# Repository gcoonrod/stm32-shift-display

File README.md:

# STM32 Shift Display

A proof-of-concept STM32 based development board designed for experimentation with 74x595 driven 7-segment LED character displays. The sponsored revision of the board is built out as a desk clock, the "STM32 Shift Clock".

> **Building or hacking on this?** [`docs/DEVELOPMENT.md`](./docs/DEVELOPMENT.md) covers prerequisites, build and flash, the USB command set, the pin map, and what is still unimplemented.

## Current Revision — rev 2
Sponsored by: 

Due to a generous sponsorship from PCBWay the current hardware revision (rev 2) includes a number of substantial design changes over the first revision:
-  All SMD components from rev 0 moved to the back.
-  Most THT components from rev 0 changed to hand-solder friendly SMD components.
-  Supercap backup for VBAT switched to more common CR2032 battery holder.
-  Addition of ESD IC for the USB connection and a correction for an issue with the USB FS series and pull-up resistors.
-  Move to a 4 layer PCB and use of via-in-pad resin plug with copper capping to simplify routing.
-  Addition of an aluminum sheet metal stand.
-  Remap latch OE pin and user LED pins to PWM capable outputs.
-  Break out UART3 "just in case".

Full schematic for this revision: [STM32ShiftDisplayRev2.pdf](./hardware/assets/STM32ShiftDisplayRev2.pdf)

### Revision Objectives
Issues with the USB connection in the first revision made a new revision necessary in order to support UART communication over the USB connection. While the USB termination bug was the primary driver for spinning a new board, there were also a few other short comings of the original design that became apparent during firmware development. The choice of shift registers to drive the LED displays instead of multiplexing made writing the display driver code simple but gave up the brightness control (from PoV) that comes "for free" with that approach. The 74HC595 has an output enable control signal that _maybe_ could be used to achieve a similar effect, so this revision includes a remapping of some of the signals, including the user LEDs, to pins on the MCU that support hardware PWM. 

As the objective of this project is as much learning as arriving at a finished "product", I took the opportunity to try out a number of new things as well. Did you know that PCBWay does sheet metal bending?

### Pushing the Envelope
With a green light to "showcase capabilities" from PCBWay, I wanted to make something worth showing off. After reviewing the website and discovering their 3D printing/CNC milling service I decided to design something that would take advantage of more than just PCBWay's PCB printing capabilities. While the core of this project would remain a development board for STM32F1 hardware and software design, this sponsored revision would be the "STM32 Shift Clock". After a brief affair with a split board design I landed on the simple board and stand design above. This design allowed me to highlight three of PCBWay's capabilities that make them great board partners for hobbyists and professionals alike. First, the PCB is a 4-layer design utilizing [via-in-pad to simplify the routing](./hardware/assets/via-in-pad.PNG) between the shift registers and LEDs characters. PCBWay's engineers were great to work with on this and made the process of indicating which vias needed to be filled and capped simple. Which was really great because KiCad does not currently have a way to indicate if a specific via should be filled. Second, I moved all of the tiny (i.e. too hard to hand solder) components to the back of the board and relied on PCBWay's turnkey PCB assembly service to source the parts and do the hard work of getting all those tiny bits in the right spots. Again, PCBWay's engineers made the process of approving the parts selection and confirming placement and orientation easy. I used LCSC as the supplier for all of the parts on this board and all I had to do was indicate the LCSC part numbers and PCBWay took care of the rest. Their engineers even sent pictures of the boards in production so that I could visually inspect all of the parts placements. And finally, the stand. I've only ever dabbled in 3D printing and certainly never with metal. So when I saw that PCBWay could do low volume sheet metal bending I had to try it out. What followed was a caffeine fueled afternoon of YouTube tutorials and frustrating attempts to get the idea in my head out into FreeCAD. In the end I went with a very simple design that displays the PCB nicely while keeping it from tipping/sliding when pressing the buttons. I chose 5052 Aluminum with a bead blasted and anodized finish to match the PCB. Given the materials and manual labor involved I was really pleased with how reasonable the quoted cost was per piece. All in all I was very impressed with my interactions with PCBWay for this project. From the initial design submissions to the engineering verification and the customer service interactions PCBWay helped me take an idea from mind to matter and I look forward to working with them again on my future projects.

### A note on revision numbers

This board is called **rev 2** here and in `stm32-shift-display.kicad_sch`, but the
sources disagree and all of them describe this same physical board:

| Source | Says |
| --- | --- |
| Schematic title block, `STM32ShiftDisplayRev2.pdf` | rev 2 |
| Git branch `feature/board-rev2`, commit "Initial rev2 design" | rev 2 |
| `stm32-shift-display.kicad_pcb` title block | rev 1 *(stale)* |
| Photo and model assets — `rev1.jpg`, `board_and_stand_rev1.jpg`, `stm32-shift-display_rev1.step` | rev 1 *(same board)* |

The `.kicad_pcb` title block is corrected only when the board is next opened in
KiCad — see [Hardware files](./docs/DEVELOPMENT.md#hardware-files) for why that is
deliberately deferred.

## Firmware

The firmware keeps time on the MCU's RTC and exposes a small command console over
USB CDC, which [`software/timesync`](./software/timesync) uses to compare and correct
the clock against NTP. The on-device menu and display brightness control are not
finished. [`docs/DEVELOPMENT.md`](./docs/DEVELOPMENT.md) has the command set, the
known defects, and what is left to build.

## Schematic

## Board Render

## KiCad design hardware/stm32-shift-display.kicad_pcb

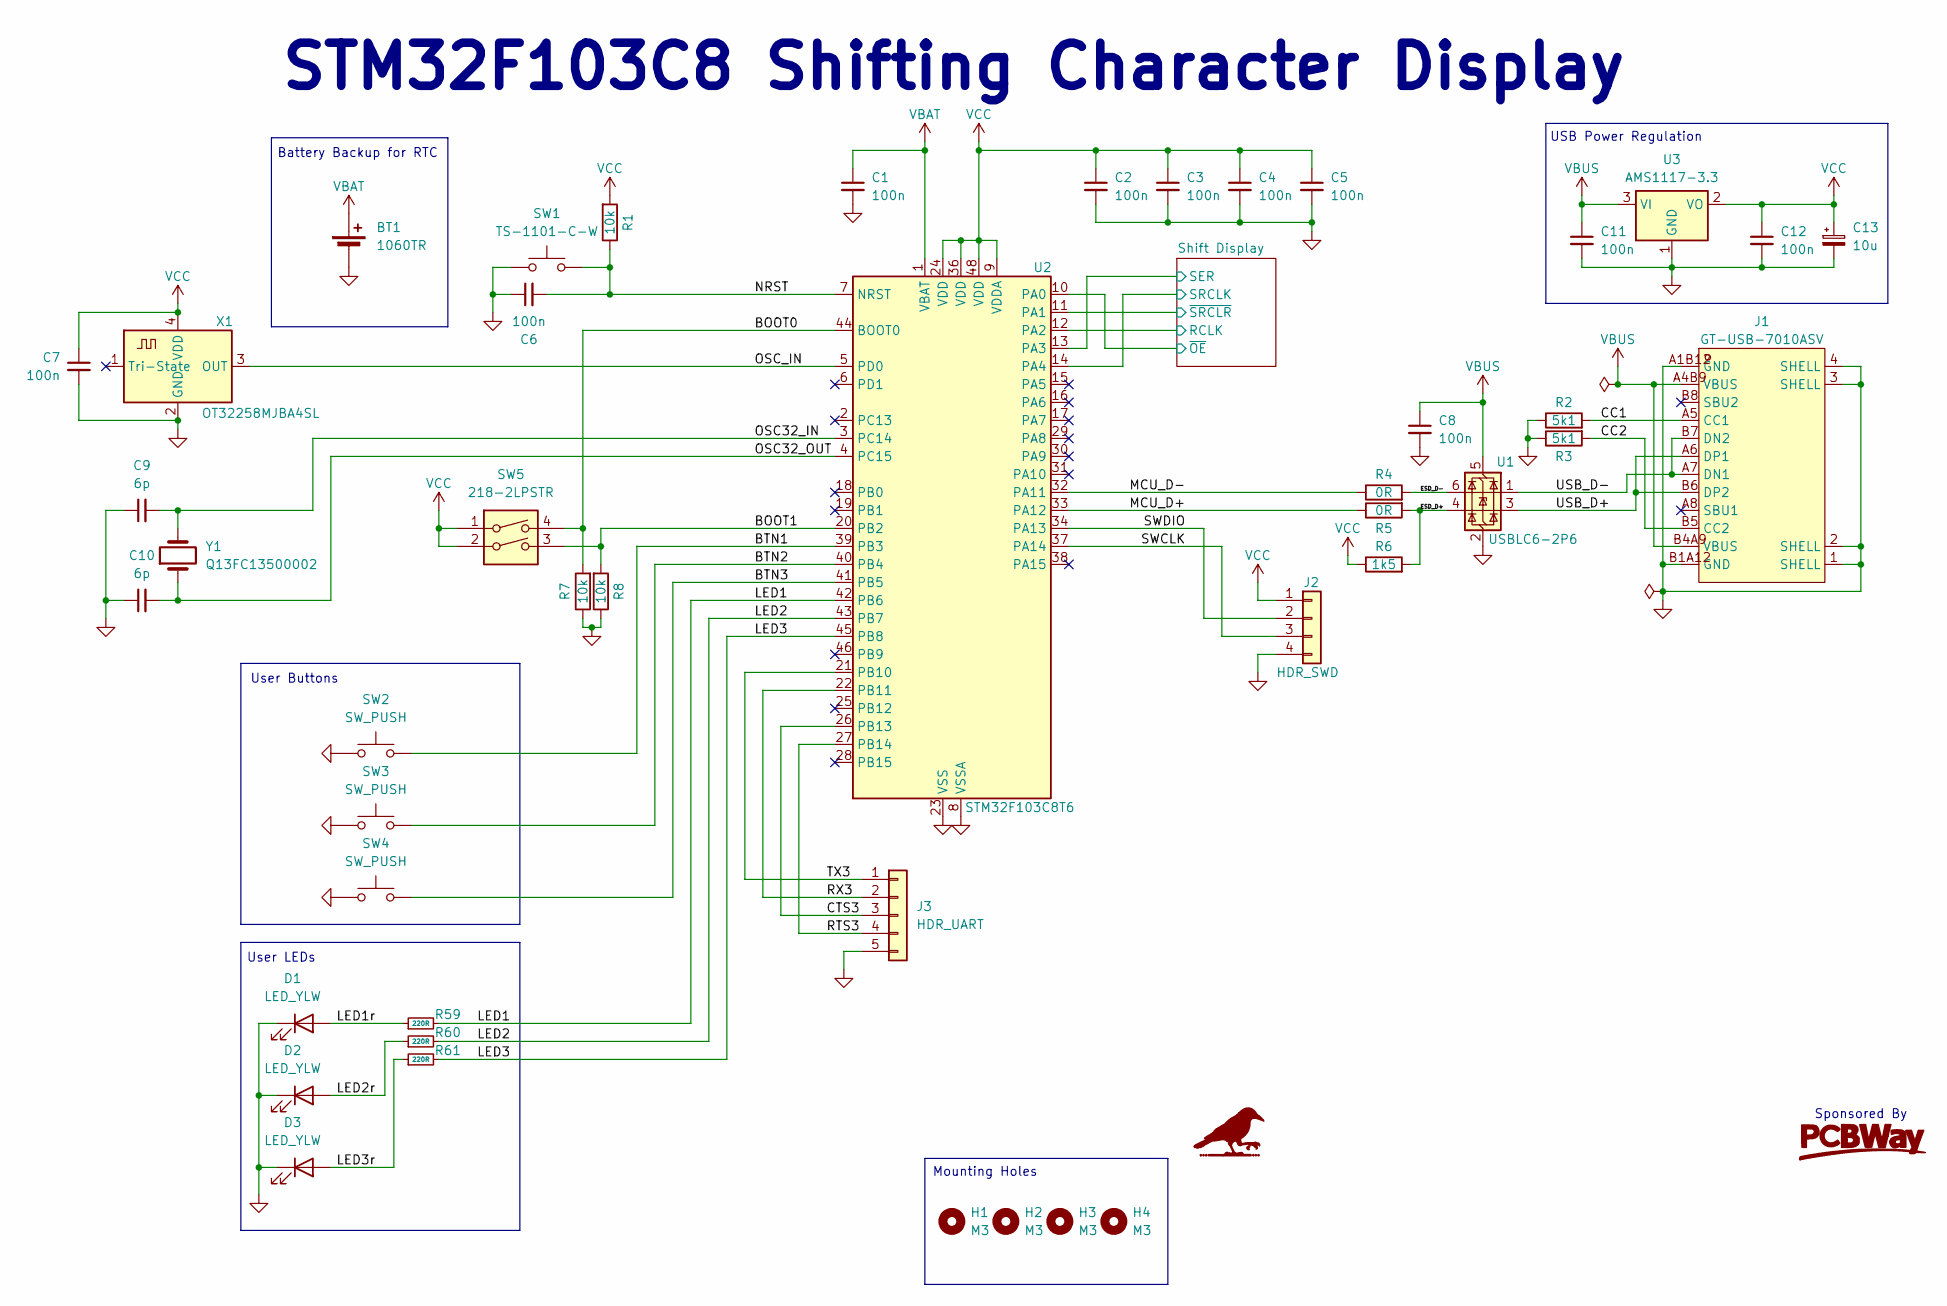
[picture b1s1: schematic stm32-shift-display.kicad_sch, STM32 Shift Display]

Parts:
BT1: 1060TR; BatteryHolder_Keystone_1060_1x2032; Mouser Part 534-1060TR
C1, C2, C3, C4, C5, C6, C7, C8: 100n; C_0402_1005Metric; LCSC Part C307331
C9, C10: 6p; C_0402_1005Metric; LCSC Part C2894321
C11, C12: 100n; C_0805_2012Metric; LCSC Part C28233
C13: 10u; CP_EIA-3216-18_Kemet-A; LCSC Part C7171
D1, D2, D3: LED_YLW; LED_D3.0mm
H1, H2, H3, H4: M3; MountingHole_3.2mm_M3_ISO7380
J1: GT-USB-7010ASV; USB-C-SMD_G-SWITCH_GT-USB-7010ASV; LCSC Part C2988369
J2: HDR_SWD; PinHeader_1x04_P2.54mm_Vertical
J3: HDR_UART; PinHeader_1x05_P2.54mm_Vertical
R1, R7, R8: 10k; R_0402_1005Metric; LCSC Part C25744
R2, R3: 5k1; R_0402_1005Metric; LCSC Part C25905
R4, R5: 0R; R_0402_1005Metric; LCSC Part C17168
R6: 1k5; R_0402_1005Metric; LCSC Part C25867
R59, R60, R61: 220R; R_0603_1608Metric; MFR Part 0603WAF2200T5E; LCSC Part C22962
SW1: TS-1101-C-W; SW-SMD_L6.0-W3.3-LS8.0; LCSC Part C318938
SW2, SW3, SW4: SW_PUSH; TS046643BK160SMT; Mouser Part 179-TS046673BK260SMT
SW5: 218-2LPSTR; SW_DIP_SPSTx02_Slide_Copal_CHS-02B_W7.62mm_P1.27mm; LCSC Part C2961921
U1: USBLC6-2P6; SOT-666; LCSC Part C2827693
U2: STM32F103C8T6; LQFP-48_7x7mm_P0.5mm; LCSC Part C8734
U3: AMS1117-3.3; SOT-223-3_TabPin2; LCSC Part C6186
X1: OT32258MJBA4SL; Crystal_SMD_3225-4Pin_3.2x2.5mm; LCSC Part C717687
Y1: Q13FC13500002; Crystal_SMD_3215-2Pin_3.2x1.5mm; LCSC Part C48615

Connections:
/BOOT0: R7.2, SW5.4, U2.44 (BOOT0)
/BOOT1: R8.2, SW5.3, U2.20 (PB2)
/BTN1: SW2.2, U2.39 (PB3)
/BTN2: SW3.2, U2.40 (PB4)
/BTN3: SW4.2, U2.41 (PB5)
/CC1: J1.A5 (CC1), R2.2
/CC2: J1.B5 (CC2), R3.2
/CTS3: J3.3, U2.26 (PB13)
/ESD_D+: R5.2, R6.2, U1.4 (I/O2)
/ESD_D-: R4.2, U1.6 (I/O1)
/LED1: R59.2, U2.42 (PB6)
/LED1r: D1.2 (A), R59.1
/LED2: R60.2, U2.43 (PB7)
/LED2r: D2.2 (A), R60.1
/LED3: R61.2, U2.45 (PB8)
/LED3r: D3.2 (A), R61.1
/MCU_D+: R5.1, U2.33 (PA12)
/MCU_D-: R4.1, U2.32 (PA11)
/NRST: C6.2, R1.1, SW1.2, U2.7 (NRST)
/OSC32_IN: C9.2, U2.3 (PC14), Y1.2
/OSC32_OUT: C10.2, U2.4 (PC15), Y1.1
/OSC_IN: U2.5 (PD0), X1.3 (OUT)
/RTS3: J3.4, U2.27 (PB14)
/RX3: J3.2, U2.22 (PB11)
/SWCLK: J2.3, U2.37 (PA14)
/SWDIO: J2.2, U2.34 (PA13)
/Shift Display/RCLK: U2.12 (PA2); also elsewhere on the board
/Shift Display/SER: U2.13 (PA3); also elsewhere on the board
/Shift Display/SRCLK: U2.14 (PA4); also elsewhere on the board
/Shift Display/~OE: U2.10 (PA0); also elsewhere on the board
/Shift Display/~SRCLR: U2.11 (PA1); also elsewhere on the board
/TX3: J3.1, U2.21 (PB10)
/USB_D+: J1.A6 (DP1), J1.B6 (DP2), U1.3 (I/O2)
/USB_D-: J1.A7 (DN1), J1.B7 (DN2), U1.1 (I/O1)
GND: BT1.2 (-), C1.2, C2.2, C3.2, C4.2, C5.2, C6.1, C7.2, C8.2, C9.1, C10.1, C11.2, C12.2, C13.2, D1.1 (K), D2.1 (K), D3.1 (K), J1.1 (SHELL), J1.2 (SHELL), J1.3 (SHELL), J1.4 (SHELL), J1.A1B12 (GND), J1.B1A12 (GND), J2.4, J3.5, R2.1, R3.1, R7.1, R8.1, SW1.1, SW2.1, SW3.1, SW4.1, U1.2 (GND), U2.8 (VSSA), U2.23 (VSS), U2.35 (VSS), U2.47 (VSS), U3.1 (GND), X1.2 (GND); also elsewhere on the board
VBAT: BT1.1 (+), C1.1, U2.1 (VBAT)
VBUS: C8.1, C11.1, J1.A4B9 (VBUS), J1.B4A9 (VBUS), U1.5 (VBUS), U3.3 (VI)
VCC: C2.1, C3.1, C4.1, C5.1, C7.1, C12.1, C13.1, J2.1, R1.2, R6.1, SW5.1, SW5.2, U2.9 (VDDA), U2.24 (VDD), U2.36 (VDD), U2.48 (VDD), U3.2 (VO), X1.4 (VDD); also elsewhere on the board

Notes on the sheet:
Battery Backup for RTC
Mounting Holes
User LEDs
USB Power Regulation
User Buttons
Sponsored By
STM32F103C8 Shifting Character Display

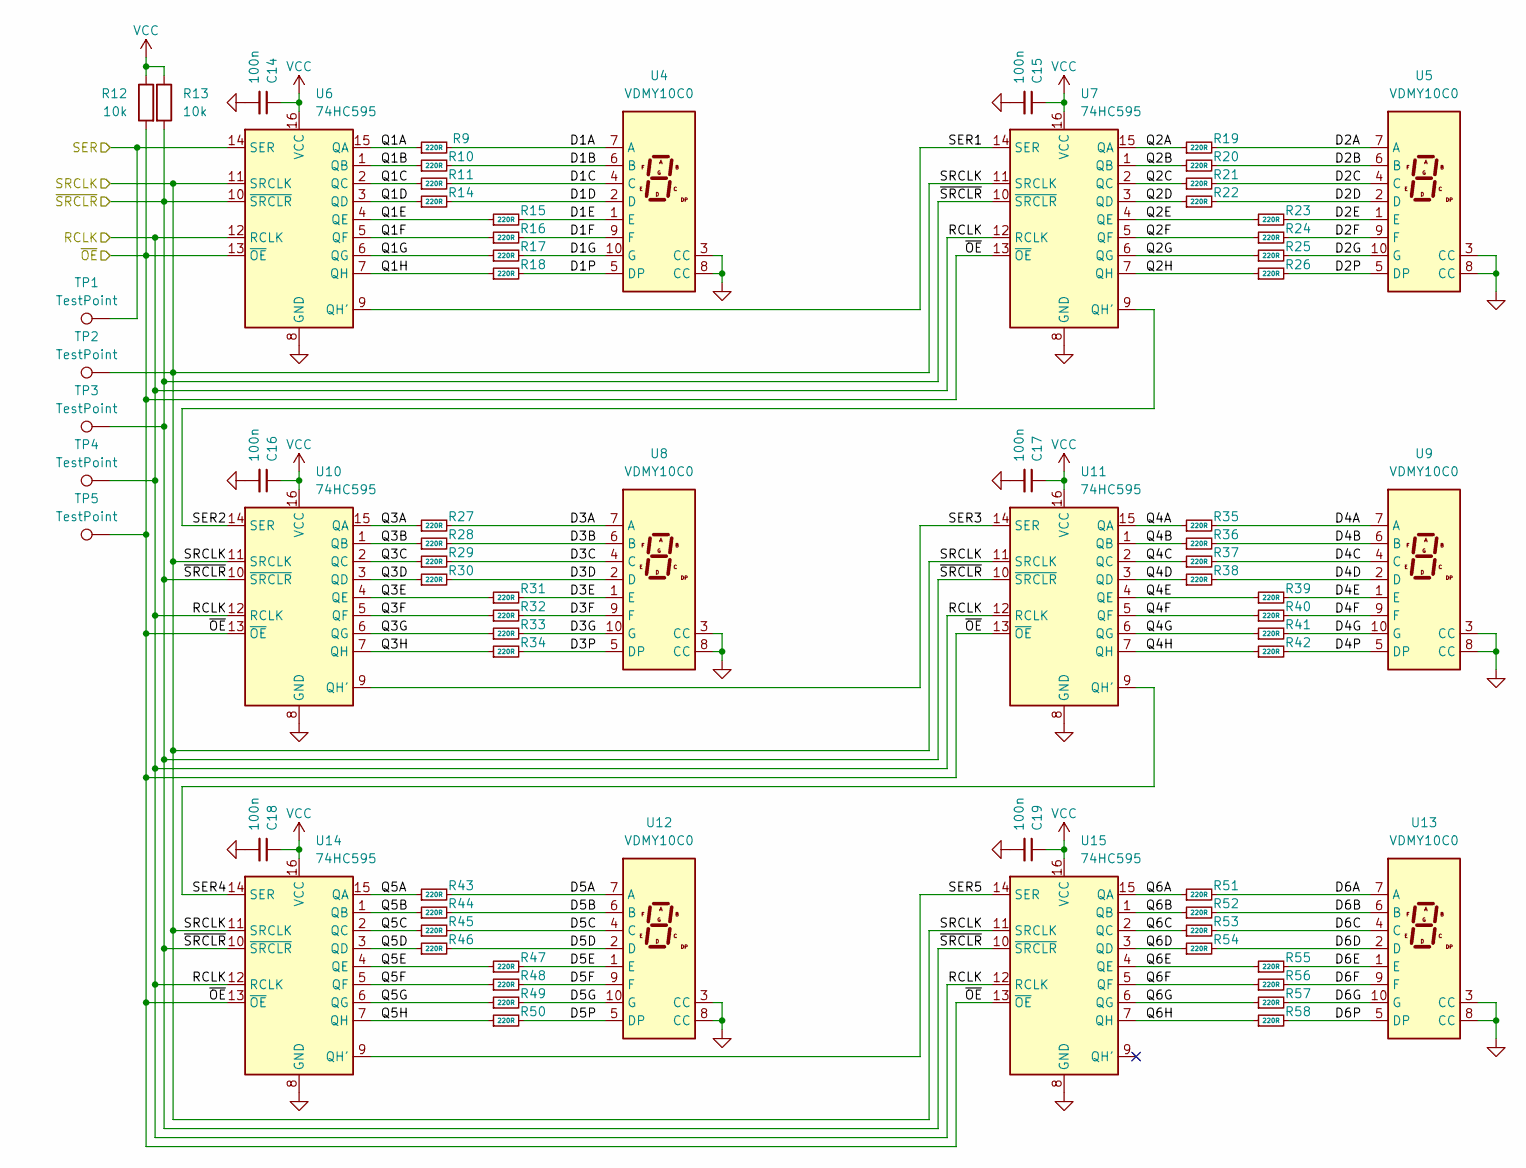
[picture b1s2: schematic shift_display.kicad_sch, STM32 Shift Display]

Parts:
C14, C15, C16, C17, C18, C19: 100n; C_0402_1005Metric; LCSC Part C307331
R9, R10, R11, R14, R15, R16, R17, R18, R19, R20, R21, R22, R23, R24, R25, R26, R27, R28, R29, R30, R31, R32, R33, R34, R35, R36, R37, R38, R39, R40, R41, R42, R43, R44, R45, R46, R47, R48, R49, R50, R51, R52, R53, R54, R55, R56, R57, R58: 220R; R_0603_1608Metric; MFR Part 0603WAF2200T5E; LCSC Part C22962
R12, R13: 10k; R_0402_1005Metric; LCSC Part C25744
TP1, TP2, TP3, TP4, TP5: TestPoint; TestPoint_Pad_D1.5mm
U4, U5, U8, U9, U12, U13: VDMY10C0; VDMx10x0; MFR Part VDMY10C0; Mouser Part 78-VDMY10C0
U6, U7, U10, U11, U14, U15: 74HC595; SOIC-16_3.9x9.9mm_P1.27mm; LCSC Part C5947

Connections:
/Shift Display/D1A: R9.2, U4.7 (A)
/Shift Display/D1B: R10.2, U4.6 (B)
/Shift Display/D1C: R11.2, U4.4 (C)
/Shift Display/D1D: R14.2, U4.2 (D)
/Shift Display/D1E: R15.2, U4.1 (E)
/Shift Display/D1F: R16.2, U4.9 (F)
/Shift Display/D1G: R17.2, U4.10 (G)
/Shift Display/D1P: R18.2, U4.5 (DP)
/Shift Display/D2A: R19.2, U5.7 (A)
/Shift Display/D2B: R20.2, U5.6 (B)
/Shift Display/D2C: R21.2, U5.4 (C)
/Shift Display/D2D: R22.2, U5.2 (D)
/Shift Display/D2E: R23.2, U5.1 (E)
/Shift Display/D2F: R24.2, U5.9 (F)
/Shift Display/D2G: R25.2, U5.10 (G)
/Shift Display/D2P: R26.2, U5.5 (DP)
/Shift Display/D3A: R27.2, U8.7 (A)
/Shift Display/D3B: R28.2, U8.6 (B)
/Shift Display/D3C: R29.2, U8.4 (C)
/Shift Display/D3D: R30.2, U8.2 (D)
/Shift Display/D3E: R31.2, U8.1 (E)
/Shift Display/D3F: R32.2, U8.9 (F)
/Shift Display/D3G: R33.2, U8.10 (G)
/Shift Display/D3P: R34.2, U8.5 (DP)
/Shift Display/D4A: R35.2, U9.7 (A)
/Shift Display/D4B: R36.2, U9.6 (B)
/Shift Display/D4C: R37.2, U9.4 (C)
/Shift Display/D4D: R38.2, U9.2 (D)
/Shift Display/D4E: R39.2, U9.1 (E)
/Shift Display/D4F: R40.2, U9.9 (F)
/Shift Display/D4G: R41.2, U9.10 (G)
/Shift Display/D4P: R42.2, U9.5 (DP)
/Shift Display/D5A: R43.2, U12.7 (A)
/Shift Display/D5B: R44.2, U12.6 (B)
/Shift Display/D5C: R45.2, U12.4 (C)
/Shift Display/D5D: R46.2, U12.2 (D)
/Shift Display/D5E: R47.2, U12.1 (E)
/Shift Display/D5F: R48.2, U12.9 (F)
/Shift Display/D5G: R49.2, U12.10 (G)
/Shift Display/D5P: R50.2, U12.5 (DP)
/Shift Display/D6A: R51.2, U13.7 (A)
/Shift Display/D6B: R52.2, U13.6 (B)
/Shift Display/D6C: R53.2, U13.4 (C)
/Shift Display/D6D: R54.2, U13.2 (D)
/Shift Display/D6E: R55.2, U13.1 (E)
/Shift Display/D6F: R56.2, U13.9 (F)
/Shift Display/D6G: R57.2, U13.10 (G)
/Shift Display/D6P: R58.2, U13.5 (DP)
/Shift Display/Q1A: R9.1, U6.15 (QA)
/Shift Display/Q1B: R10.1, U6.1 (QB)
/Shift Display/Q1C: R11.1, U6.2 (QC)
/Shift Display/Q1D: R14.1, U6.3 (QD)
/Shift Display/Q1E: R15.1, U6.4 (QE)
/Shift Display/Q1F: R16.1, U6.5 (QF)
/Shift Display/Q1G: R17.1, U6.6 (QG)
/Shift Display/Q1H: R18.1, U6.7 (QH)
/Shift Display/Q2A: R19.1, U7.15 (QA)
/Shift Display/Q2B: R20.1, U7.1 (QB)
/Shift Display/Q2C: R21.1, U7.2 (QC)
/Shift Display/Q2D: R22.1, U7.3 (QD)
/Shift Display/Q2E: R23.1, U7.4 (QE)
/Shift Display/Q2F: R24.1, U7.5 (QF)
/Shift Display/Q2G: R25.1, U7.6 (QG)
/Shift Display/Q2H: R26.1, U7.7 (QH)
/Shift Display/Q3A: R27.1, U10.15 (QA)
/Shift Display/Q3B: R28.1, U10.1 (QB)
/Shift Display/Q3C: R29.1, U10.2 (QC)
/Shift Display/Q3D: R30.1, U10.3 (QD)
/Shift Display/Q3E: R31.1, U10.4 (QE)
/Shift Display/Q3F: R32.1, U10.5 (QF)
/Shift Display/Q3G: R33.1, U10.6 (QG)
/Shift Display/Q3H: R34.1, U10.7 (QH)
/Shift Display/Q4A: R35.1, U11.15 (QA)
/Shift Display/Q4B: R36.1, U11.1 (QB)
/Shift Display/Q4C: R37.1, U11.2 (QC)
/Shift Display/Q4D: R38.1, U11.3 (QD)
/Shift Display/Q4E: R39.1, U11.4 (QE)
/Shift Display/Q4F: R40.1, U11.5 (QF)
/Shift Display/Q4G: R41.1, U11.6 (QG)
/Shift Display/Q4H: R42.1, U11.7 (QH)
/Shift Display/Q5A: R43.1, U14.15 (QA)
/Shift Display/Q5B: R44.1, U14.1 (QB)
/Shift Display/Q5C: R45.1, U14.2 (QC)
/Shift Display/Q5D: R46.1, U14.3 (QD)
/Shift Display/Q5E: R47.1, U14.4 (QE)
/Shift Display/Q5F: R48.1, U14.5 (QF)
/Shift Display/Q5G: R49.1, U14.6 (QG)
/Shift Display/Q5H: R50.1, U14.7 (QH)
/Shift Display/Q6A: R51.1, U15.15 (QA)
/Shift Display/Q6B: R52.1, U15.1 (QB)
/Shift Display/Q6C: R53.1, U15.2 (QC)
/Shift Display/Q6D: R54.1, U15.3 (QD)
/Shift Display/Q6E: R55.1, U15.4 (QE)
/Shift Display/Q6F: R56.1, U15.5 (QF)
/Shift Display/Q6G: R57.1, U15.6 (QG)
/Shift Display/Q6H: R58.1, U15.7 (QH)
/Shift Display/RCLK: TP4.1, U6.12 (RCLK), U7.12 (RCLK), U10.12 (RCLK), U11.12 (RCLK), U14.12 (RCLK), U15.12 (RCLK); also elsewhere on the board
/Shift Display/SER: TP1.1, U6.14 (SER); also elsewhere on the board
/Shift Display/SER1: U6.9 (QH'), U7.14 (SER)
/Shift Display/SER2: U7.9 (QH'), U10.14 (SER)
/Shift Display/SER3: U10.9 (QH'), U11.14 (SER)
/Shift Display/SER4: U11.9 (QH'), U14.14 (SER)
/Shift Display/SER5: U14.9 (QH'), U15.14 (SER)
/Shift Display/SRCLK: TP2.1, U6.11 (SRCLK), U7.11 (SRCLK), U10.11 (SRCLK), U11.11 (SRCLK), U14.11 (SRCLK), U15.11 (SRCLK); also elsewhere on the board
/Shift Display/~OE: R12.2, TP5.1, U6.13 (~OE), U7.13 (~OE), U10.13 (~OE), U11.13 (~OE), U14.13 (~OE), U15.13 (~OE); also elsewhere on the board
/Shift Display/~SRCLR: R13.2, TP3.1, U6.10 (~SRCLR), U7.10 (~SRCLR), U10.10 (~SRCLR), U11.10 (~SRCLR), U14.10 (~SRCLR), U15.10 (~SRCLR); also elsewhere on the board
GND: C14.2, C15.2, C16.2, C17.2, C18.2, C19.2, U4.3 (CC), U4.8 (CC), U5.3 (CC), U5.8 (CC), U6.8 (GND), U7.8 (GND), U8.3 (CC), U8.8 (CC), U9.3 (CC), U9.8 (CC), U10.8 (GND), U11.8 (GND), U12.3 (CC), U12.8 (CC), U13.3 (CC), U13.8 (CC), U14.8 (GND), U15.8 (GND); also elsewhere on the board
VCC: C14.1, C15.1, C16.1, C17.1, C18.1, C19.1, R12.1, R13.1, U6.16 (VCC), U7.16 (VCC), U10.16 (VCC), U11.16 (VCC), U14.16 (VCC), U15.16 (VCC); also elsewhere on the board

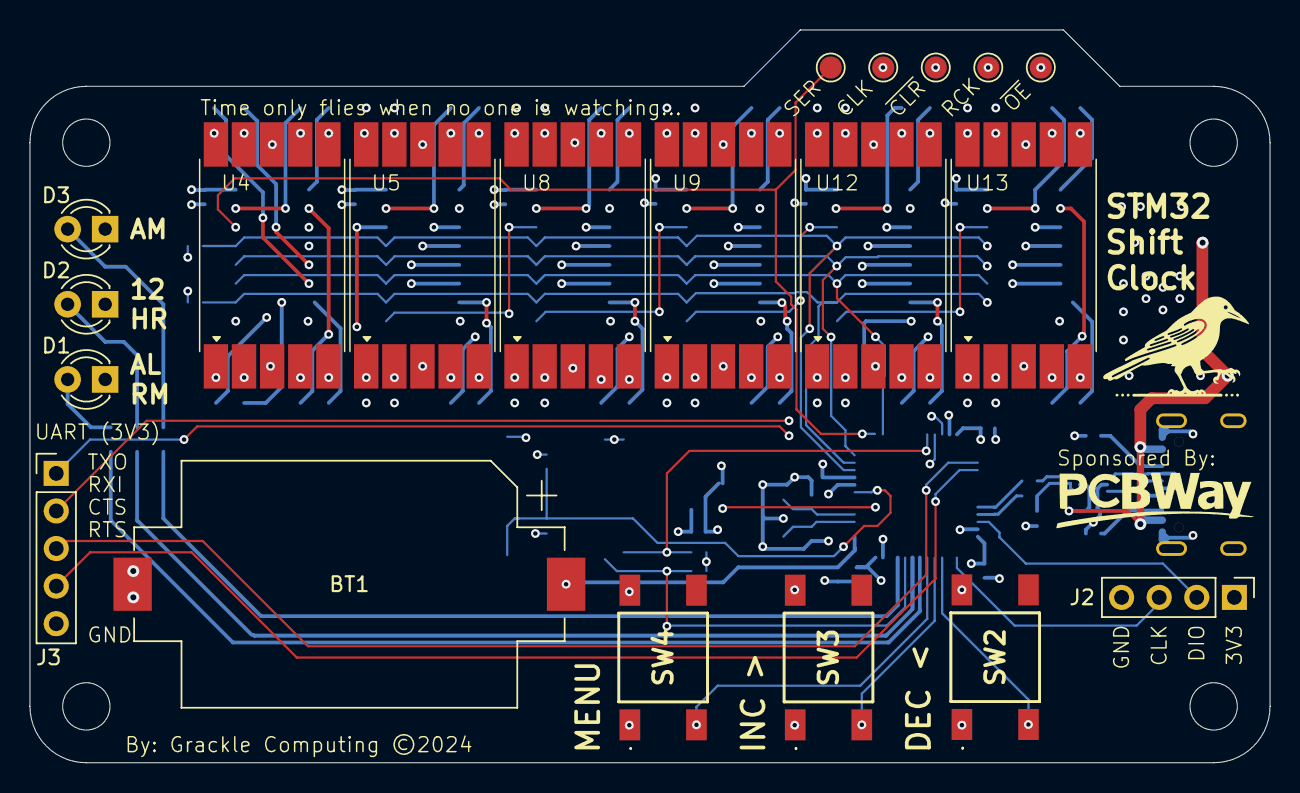
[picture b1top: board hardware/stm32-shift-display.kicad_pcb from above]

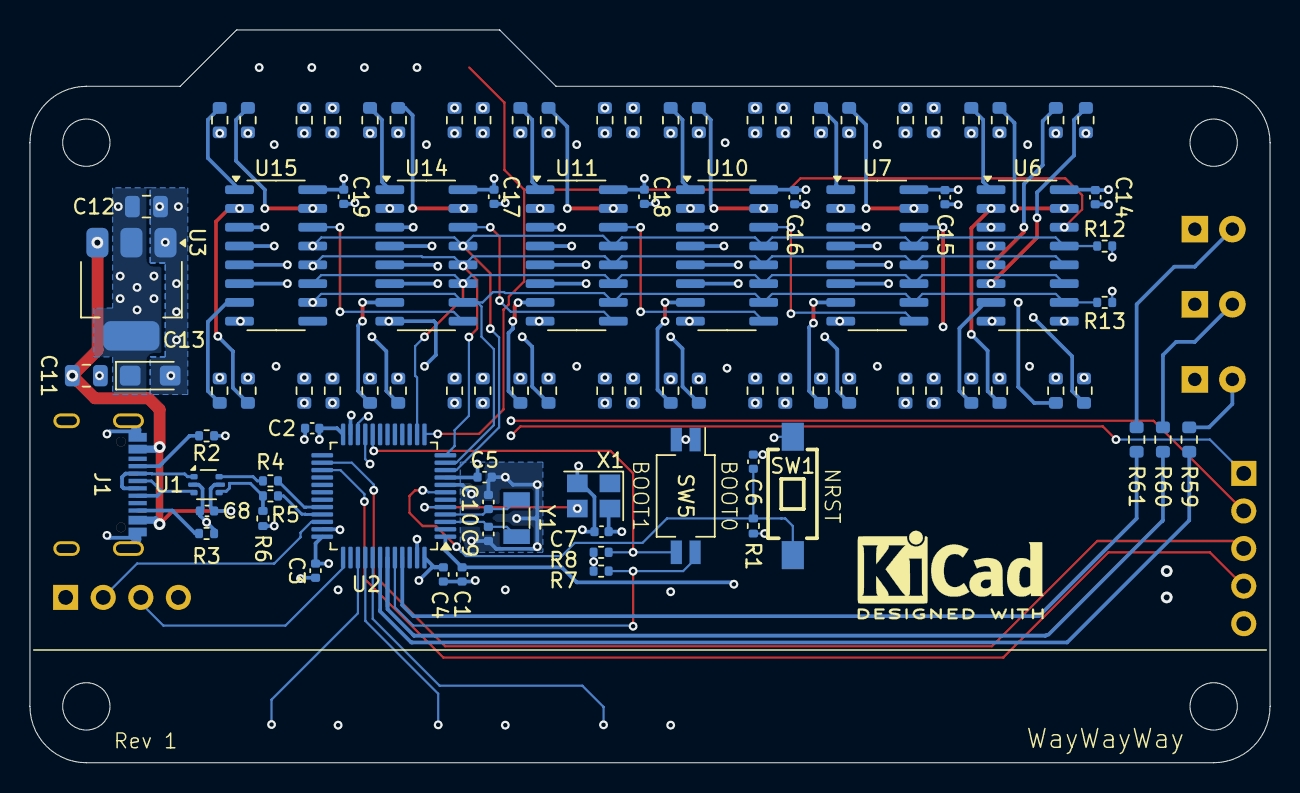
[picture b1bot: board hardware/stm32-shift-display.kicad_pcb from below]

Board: 4 copper layers, 83.8 x 49.5 mm, 118 parts (94 on the bottom side), 139 nets.

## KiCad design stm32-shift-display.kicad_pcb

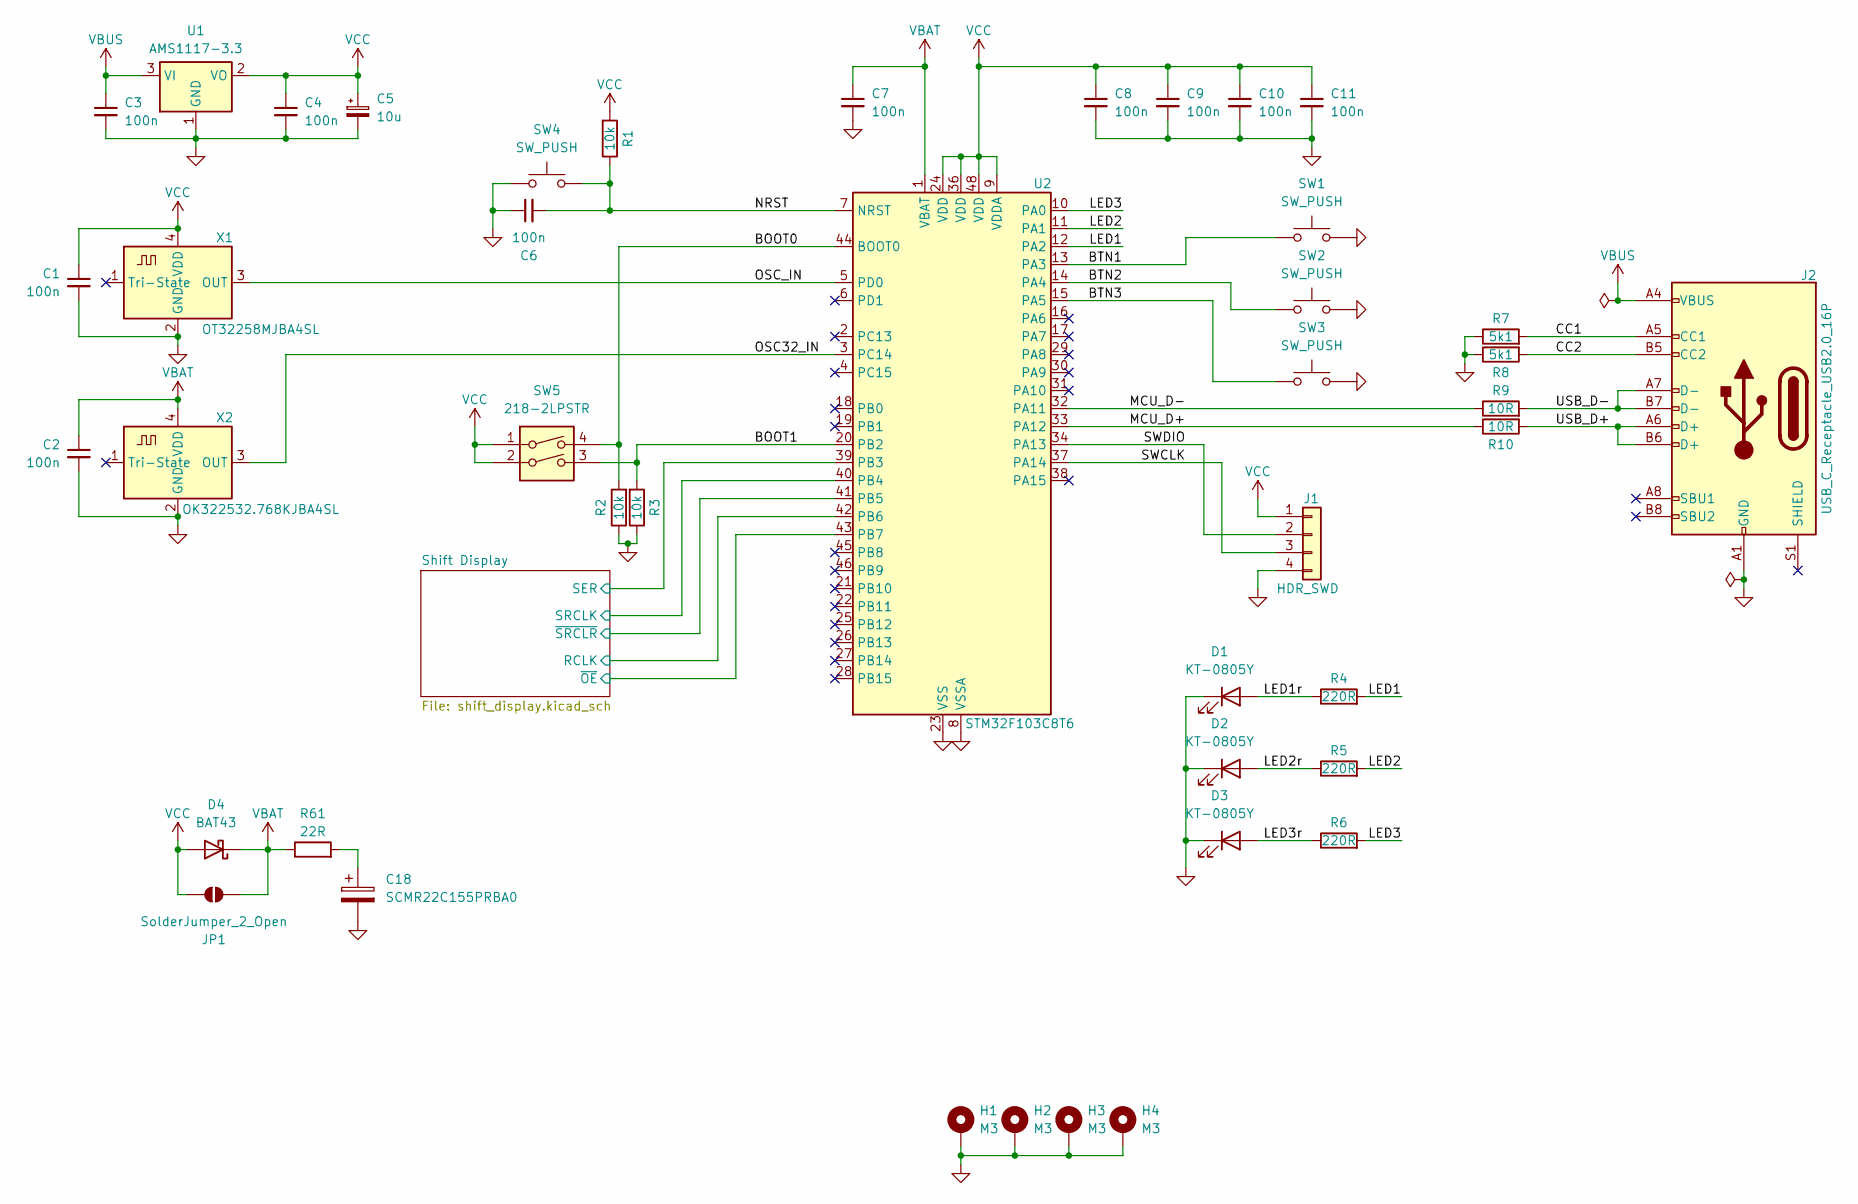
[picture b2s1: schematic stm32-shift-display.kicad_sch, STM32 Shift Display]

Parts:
C1, C2, C6, C7, C8, C9, C10, C11: 100n; C_0402_1005Metric; MFR Part CL05B104KB54PNC; JLCPCB Part C307331
C3, C4: 100n; C_0805_2012Metric; JLCPCB Part C28233
C5: 10u; CP_EIA-3216-18_Kemet-A; MFR Part TAJA106K016RNJ; JLCPCB Part C7171
C18: SCMR22C155PRBA0; Mouser Part 581-SCMR22C155PRBA0
D1, D2, D3: KT-0805Y; LED_0805_2012Metric; JLCPCB Part C2296
D4: BAT43; D_DO-35_SOD27_P7.62mm_Horizontal
H1, H2, H3, H4: M3; MountingHole_3.2mm_M3_Pad_Via
J1: HDR_SWD; PinHeader_1x04_P2.54mm_Vertical
J2: USB_C_Receptacle_USB2.0_16P; USB_C_Receptacle_HCTL_HC-TYPE-C-16P-01A; JLCPCB Part C2997433
JP1: SolderJumper_2_Open; SolderJumper-2_P1.3mm_Open_RoundedPad1.0x1.5mm
R1, R2, R3: 10k; R_0402_1005Metric; JLCPCB Part C25744
R4, R5, R6: 220R; R_0603_1608Metric; MFR Part 0603WAF2200T5E; JLCPCB Part C22962
R7, R8: 5k1; R_0402_1005Metric; JLCPCB Part C25905
R9, R10: 10R; R_0402_1005Metric; JLCPCB Part C25077
R61: 22R; R_Axial_DIN0207_L6.3mm_D2.5mm_P7.62mm_Horizontal
SW1, SW2, SW3, SW4: SW_PUSH; SW_PUSH_6mm
SW5: 218-2LPSTR; SW_DIP_SPSTx02_Slide_Copal_CHS-02B_W7.62mm_P1.27mm; JLCPCB Part C2961921
U1: AMS1117-3.3; SOT-223-3_TabPin2; JLCPCB Part C6186
U2: STM32F103C8T6; LQFP-48_7x7mm_P0.5mm; JLCPCB Part C8734
X1: OT32258MJBA4SL; Crystal_SMD_3225-4Pin_3.2x2.5mm; JLCPCB Part C717687
X2: OK322532.768KJBA4SL; Crystal_SMD_3225-4Pin_3.2x2.5mm; JLCPCB Part C725996

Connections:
/BOOT0: R2.2, SW5.4, U2.44 (BOOT0)
/BOOT1: R3.2, SW5.3, U2.20 (PB2)
/BTN1: SW1.2, U2.13 (PA3)
/BTN2: SW2.2, U2.14 (PA4)
/BTN3: SW3.2, U2.15 (PA5)
/CC1: J2.A5 (CC1), R7.2
/CC2: J2.B5 (CC2), R8.2
/LED1: R4.2, U2.12 (PA2)
/LED1r: D1.2 (A), R4.1
/LED2: R5.2, U2.11 (PA1)
/LED2r: D2.2 (A), R5.1
/LED3: R6.2, U2.10 (PA0)
/LED3r: D3.2 (A), R6.1
/MCU_D+: R10.1, U2.33 (PA12)
/MCU_D-: R9.1, U2.32 (PA11)
/NRST: C6.2, R1.1, SW4.2, U2.7 (NRST)
/OSC32_IN: U2.3 (PC14), X2.3 (OUT)
/OSC_IN: U2.5 (PD0), X1.3 (OUT)
/SWCLK: J1.3, U2.37 (PA14)
/SWDIO: J1.2, U2.34 (PA13)
/Shift Display/RCLK: U2.42 (PB6); also elsewhere on the board
/Shift Display/SER: U2.39 (PB3); also elsewhere on the board
/Shift Display/SRCLK: U2.40 (PB4); also elsewhere on the board
/Shift Display/~OE: U2.43 (PB7); also elsewhere on the board
/Shift Display/~SRCLR: U2.41 (PB5); also elsewhere on the board
/USB_D+: J2.A6 (D+), J2.B6 (D+), R10.2
/USB_D-: J2.A7 (D-), J2.B7 (D-), R9.2
GND: C1.2, C2.2, C3.2, C4.2, C5.2, C6.1, C7.2, C8.2, C9.2, C10.2, C11.2, C18.2, D1.1 (K), D2.1 (K), D3.1 (K), H1.1, H2.1, H3.1, H4.1, J1.4, J2.A1 (GND), J2.A12 (GND), J2.B1 (GND), J2.B12 (GND), R2.1, R3.1, R7.1, R8.1, SW1.1, SW2.1, SW3.1, SW4.1, U1.1 (GND), U2.8 (VSSA), U2.23 (VSS), U2.35 (VSS), U2.47 (VSS), X1.2 (GND), X2.2 (GND); also elsewhere on the board
unnamed: C18.1, R61.2
VBAT: C2.1, C7.1, D4.1 (K), JP1.2 (B), R61.1, U2.1 (VBAT), X2.4 (VDD)
VBUS: C3.1, J2.A4 (VBUS), J2.A9 (VBUS), J2.B4 (VBUS), J2.B9 (VBUS), U1.3 (VI)
VCC: C1.1, C4.1, C5.1, C8.1, C9.1, C10.1, C11.1, D4.2 (A), J1.1, JP1.1 (A), R1.2, SW5.1, SW5.2, U1.2 (VO), U2.9 (VDDA), U2.24 (VDD), U2.36 (VDD), U2.48 (VDD), X1.4 (VDD); also elsewhere on the board

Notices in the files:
hardware/stm32-shift-display.kicad_pcb:
By: Grackle Computing ©2024
